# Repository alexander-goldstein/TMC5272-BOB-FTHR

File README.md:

# TMC5272-BOB-FTHR

An adapter board for connecting Adafruit Feather-format MCU boards to the TMC5272 breakout board (BOB) for prototyping applications.

**Trinamic / Analog Devices, Inc.**

## Overview

This adapter board provides a simple platform for connecting any Adafruit Feather (FTHR) form factor microcontroller to a TMC5272-BOB. The board breaks out connections including SPI, power, and control signals to facilitate rapid prototyping and evaluation of the TMC5272 stepper motor driver.

This project was designed with KiCad 10.

## Features

- Compatible with Adafruit Feather form factor MCU boards.
- Dual-row headers: Inner column accepts female headers for board insertion, outer column (optional) for male pins to probe signals or attach jumper wires.
- Flexible signal routing: CS, DIAG0, and DIAG1 are jumper-configurable to connect to any desired MCU pin.
- Test points for easy debugging.

## Board Layout

## Fabrication

Gerber files are available in the `gerber/` directory. The ZIP file in that folder can be uploaded directly to [OSH Park](https://oshpark.com/) for fabrication.

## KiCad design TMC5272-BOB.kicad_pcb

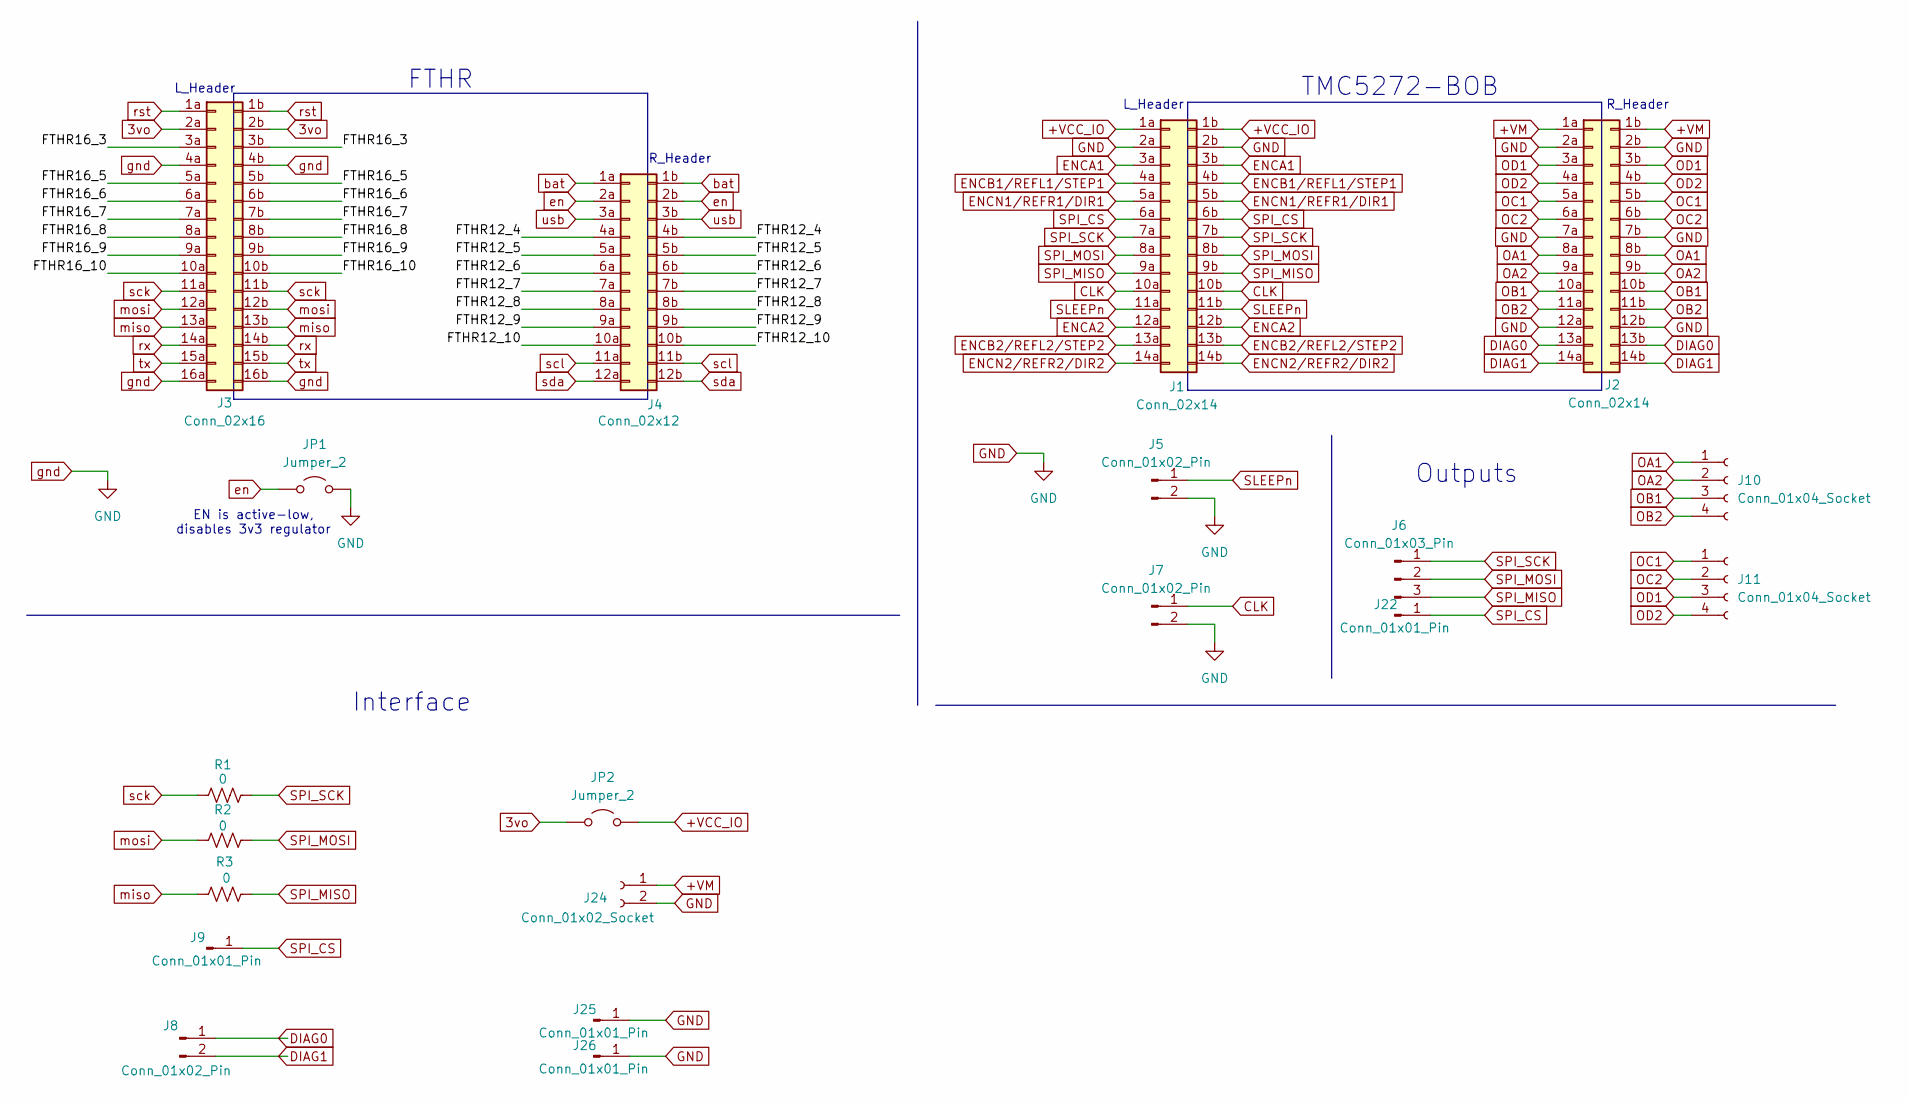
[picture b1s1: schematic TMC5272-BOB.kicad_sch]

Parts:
J1, J2: Conn_02x14; PinHeader_2x14_P2.54mm_Vertical
J3: Conn_02x16; PinSocket_2x16_P2.54mm_Vertical
J4: Conn_02x12; PinHeader_2x12_P2.54mm_Vertical
J5, J7, J8: Conn_01x02_Pin; PinHeader_1x02_P2.54mm_Vertical
J6: Conn_01x03_Pin; PinHeader_1x03_P2.54mm_Vertical
J9, J22, J25, J26: Conn_01x01_Pin; PinHeader_1x01_P2.54mm_Vertical
J10, J11: Conn_01x04_Socket; JST_XH_B4B-XH-AM_1x04_P2.50mm_Vertical
J24: Conn_01x02_Socket; JST_XH_B2B-XH-A_1x02_P2.50mm_Vertical
JP1, JP2: Jumper_2; TestPoint_2Pads_Pitch2.54mm_Drill0.8mm
R1, R2, R3: 0; R_0805_2012Metric

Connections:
3vo: J3.2a, J3.2b, JP2.1 (A)
+VCC_IO: J1.1a, J1.1b, JP2.2 (B)
+VM: J2.1a, J2.1b, J24.1
/FTHR12_4: J4.4a, J4.4b
/FTHR12_5: J4.5a, J4.5b
/FTHR12_6: J4.6a, J4.6b
/FTHR12_7: J4.7a, J4.7b
/FTHR12_8: J4.8a, J4.8b
/FTHR12_9: J4.9a, J4.9b
/FTHR12_10: J4.10a, J4.10b
/FTHR16_3: J3.3a, J3.3b
/FTHR16_5: J3.5a, J3.5b
/FTHR16_6: J3.6a, J3.6b
/FTHR16_7: J3.7a, J3.7b
/FTHR16_8: J3.8a, J3.8b
/FTHR16_9: J3.9a, J3.9b
/FTHR16_10: J3.10a, J3.10b
CLK: J1.10a, J1.10b, J7.1
DIAG0: J2.13a, J2.13b, J8.1
DIAG1: J2.14a, J2.14b, J8.2
ENCA1: J1.3a, J1.3b
ENCA2: J1.12a, J1.12b
ENCB1/REFL1/STEP1: J1.4a, J1.4b
ENCB2/REFL2/STEP2: J1.13a, J1.13b
ENCN1/REFR1/DIR1: J1.5a, J1.5b
ENCN2/REFR2/DIR2: J1.14a, J1.14b
GND: J1.2a, J1.2b, J2.2a, J2.2b, J2.7a, J2.7b, J2.12a, J2.12b, J3.4a, J3.4b, J3.16a, J3.16b, J5.2, J7.2, J24.2, J25.1, J26.1 (Pin_1_1), JP1.2 (B)
OA1: J2.8a, J2.8b, J10.1
OA2: J2.9a, J2.9b, J10.2
OB1: J2.10a, J2.10b, J10.3
OB2: J2.11a, J2.11b, J10.4
OC1: J2.5a, J2.5b, J11.1
OC2: J2.6a, J2.6b, J11.2
OD1: J2.3a, J2.3b, J11.3
OD2: J2.4a, J2.4b, J11.4
SLEEPn: J1.11a, J1.11b, J5.1
SPI_CS: J1.6a, J1.6b, J9.1 (Pin_1_1), J22.1 (Pin_1_1)
SPI_MISO: J1.9a, J1.9b, J6.3, R3.2
SPI_MOSI: J1.8a, J1.8b, J6.2, R2.2
SPI_SCK: J1.7a, J1.7b, J6.1, R1.2
bat: J4.1a, J4.1b
en: J4.2a, J4.2b, JP1.1 (A)
miso: J3.13a, J3.13b, R3.1
mosi: J3.12a, J3.12b, R2.1
rst: J3.1a, J3.1b
rx: J3.14a, J3.14b
sck: J3.11a, J3.11b, R1.1
scl: J4.11a, J4.11b
sda: J4.12a, J4.12b
tx: J3.15a, J3.15b
usb: J4.3a, J4.3b

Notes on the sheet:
L_Header
FTHR
Interface
R_Header
EN is active-low, disables 3v3 regulator
Outputs
TMC5272-BOB

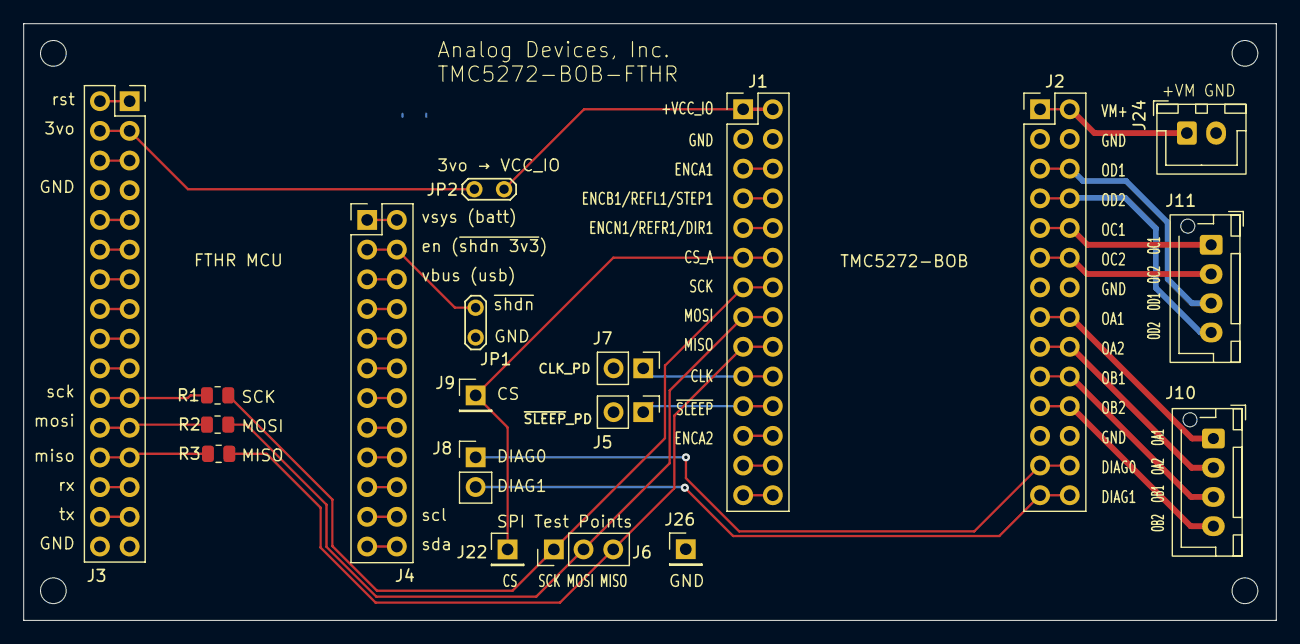
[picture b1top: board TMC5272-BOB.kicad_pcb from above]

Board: 2 copper layers, 107.2 x 51.1 mm, 19 parts (0 on the bottom side), 51 nets.

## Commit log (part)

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2026-05-12 Initial commit.
2026-05-12 Add readme.
